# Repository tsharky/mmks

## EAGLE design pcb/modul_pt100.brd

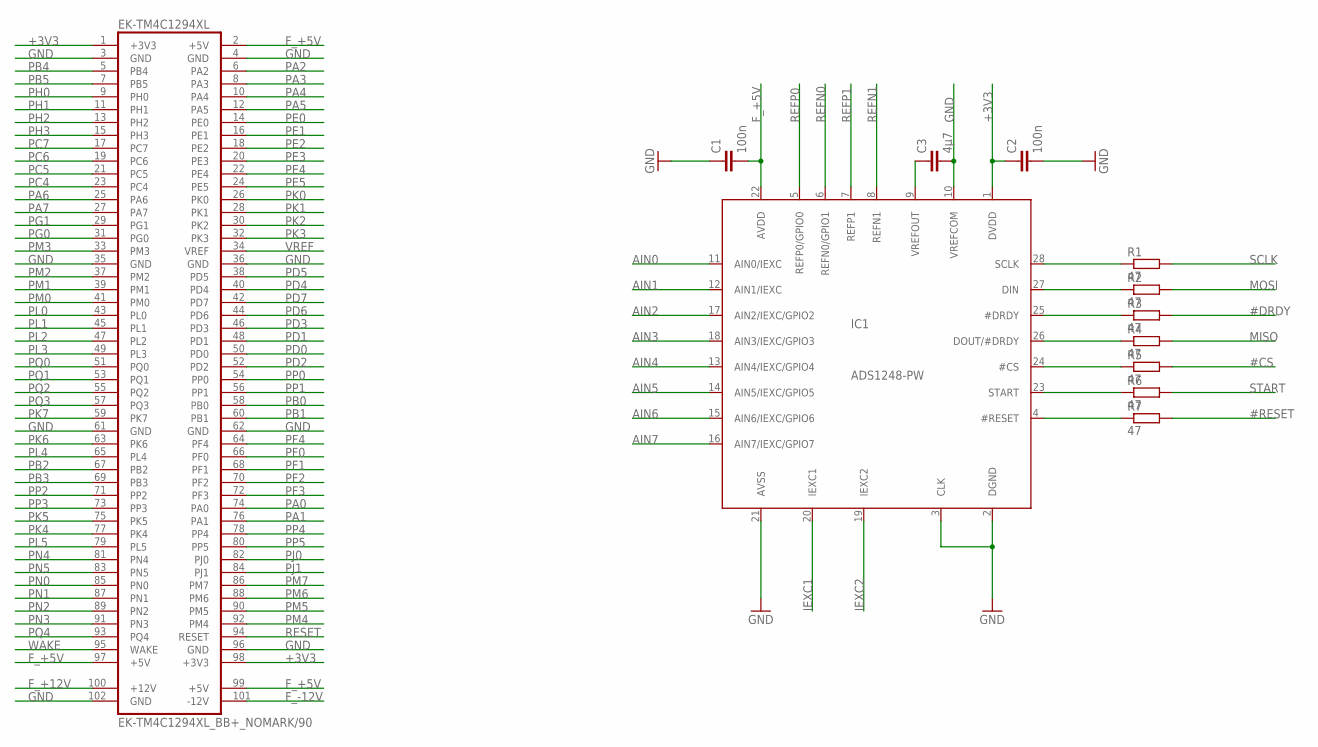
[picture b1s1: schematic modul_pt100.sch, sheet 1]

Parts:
C1, C2: 100n; C0805
C3: 4µ7; C0805
EK-TM4C1294XL: EK-TM4C1294XL_BB+_NOMARK/90
IC1: ADS1248-PW; TSSOP28
R1, R2, R3, R4, R5, R6, R7: 47; R0805

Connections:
#CS: R5.2; also elsewhere on the board
#DRDY: R3.2; also elsewhere on the board
#RESET: R7.2; also elsewhere on the board
+3V3: C2.1, EK-TM4C1294XL.1 (+3V3), EK-TM4C1294XL.98 (+3V3), IC1.1 (DVDD); also elsewhere on the board
AIN0: IC1.11 (AIN0/IEXC); also elsewhere on the board
AIN1: IC1.12 (AIN1/IEXC); also elsewhere on the board
AIN2: IC1.17 (AIN2/IEXC/GPIO2); also elsewhere on the board
AIN3: IC1.18 (AIN3/IEXC/GPIO3); also elsewhere on the board
AIN4: IC1.13 (AIN4/IEXC/GPIO4)
AIN5: IC1.14 (AIN5/IEXC/GPIO5)
AIN6: IC1.15 (AIN6/IEXC/GPIO6)
AIN7: IC1.16 (AIN7/IEXC/GPIO7)
F_+5V: C1.2, EK-TM4C1294XL.2 (+5V), EK-TM4C1294XL.97 (+5V), EK-TM4C1294XL.99 (+5V), IC1.22 (AVDD); also elsewhere on the board
F_+12V: EK-TM4C1294XL.100 (+12V); also elsewhere on the board
F_-12V: EK-TM4C1294XL.101 (-12V); also elsewhere on the board
GND: C1.1, C2.2, C3.2, EK-TM4C1294XL.3 (GND), EK-TM4C1294XL.4 (GND), EK-TM4C1294XL.35 (GND), EK-TM4C1294XL.36 (GND), EK-TM4C1294XL.61 (GND), EK-TM4C1294XL.62 (GND), EK-TM4C1294XL.96 (GND), EK-TM4C1294XL.102 (GND), IC1.2 (DGND), IC1.3 (CLK), IC1.10 (VREFCOM), IC1.21 (AVSS); also elsewhere on the board
IEXC1: IC1.20 (IEXC1); also elsewhere on the board
IEXC2: IC1.19 (IEXC2); also elsewhere on the board
MISO: R4.2; also elsewhere on the board
MOSI: R2.2; also elsewhere on the board
unnamed: C3.1, IC1.9 (VREFOUT)
unnamed: IC1.28 (SCLK), R1.1
unnamed: IC1.27 (DIN), R2.1
unnamed: IC1.25 (#DRDY), R3.1
unnamed: IC1.26 (DOUT/#DRDY), R4.1
unnamed: IC1.24 (#CS), R5.1
unnamed: IC1.23 (START), R6.1
unnamed: IC1.4 (#RESET), R7.1
PA0: EK-TM4C1294XL.74 (PA0); also elsewhere on the board
PA1: EK-TM4C1294XL.76 (PA1); also elsewhere on the board
PA2: EK-TM4C1294XL.6 (PA2); also elsewhere on the board
PA3: EK-TM4C1294XL.8 (PA3); also elsewhere on the board
PA4: EK-TM4C1294XL.10 (PA4); also elsewhere on the board
PA5: EK-TM4C1294XL.12 (PA5); also elsewhere on the board
PA6: EK-TM4C1294XL.25 (PA6); also elsewhere on the board
PA7: EK-TM4C1294XL.27 (PA7); also elsewhere on the board
PB0: EK-TM4C1294XL.58 (PB0); also elsewhere on the board
PB1: EK-TM4C1294XL.60 (PB1); also elsewhere on the board
PB2: EK-TM4C1294XL.67 (PB2); also elsewhere on the board
PB3: EK-TM4C1294XL.69 (PB3); also elsewhere on the board
PB4: EK-TM4C1294XL.5 (PB4); also elsewhere on the board
PB5: EK-TM4C1294XL.7 (PB5); also elsewhere on the board
PC4: EK-TM4C1294XL.23 (PC4); also elsewhere on the board
PC5: EK-TM4C1294XL.21 (PC5); also elsewhere on the board
PC6: EK-TM4C1294XL.19 (PC6); also elsewhere on the board
PC7: EK-TM4C1294XL.17 (PC7); also elsewhere on the board
PD0: EK-TM4C1294XL.50 (PD0); also elsewhere on the board
PD1: EK-TM4C1294XL.48 (PD1); also elsewhere on the board
PD2: EK-TM4C1294XL.52 (PD2); also elsewhere on the board
PD3: EK-TM4C1294XL.46 (PD3); also elsewhere on the board
PD4: EK-TM4C1294XL.40 (PD4); also elsewhere on the board
PD5: EK-TM4C1294XL.38 (PD5); also elsewhere on the board
PD6: EK-TM4C1294XL.44 (PD6); also elsewhere on the board
PD7: EK-TM4C1294XL.42 (PD7); also elsewhere on the board
PE0: EK-TM4C1294XL.14 (PE0); also elsewhere on the board
PE1: EK-TM4C1294XL.16 (PE1); also elsewhere on the board
PE2: EK-TM4C1294XL.18 (PE2); also elsewhere on the board
PE3: EK-TM4C1294XL.20 (PE3); also elsewhere on the board
PE4: EK-TM4C1294XL.22 (PE4); also elsewhere on the board
PE5: EK-TM4C1294XL.24 (PE5); also elsewhere on the board
PF0: EK-TM4C1294XL.66 (PF0); also elsewhere on the board
PF1: EK-TM4C1294XL.68 (PF1); also elsewhere on the board
PF2: EK-TM4C1294XL.70 (PF2); also elsewhere on the board
PF3: EK-TM4C1294XL.72 (PF3); also elsewhere on the board
PF4: EK-TM4C1294XL.64 (PF4); also elsewhere on the board
PG0: EK-TM4C1294XL.31 (PG0); also elsewhere on the board
PG1: EK-TM4C1294XL.29 (PG1); also elsewhere on the board
PH0: EK-TM4C1294XL.9 (PH0); also elsewhere on the board
PH1: EK-TM4C1294XL.11 (PH1); also elsewhere on the board
PH2: EK-TM4C1294XL.13 (PH2); also elsewhere on the board
PH3: EK-TM4C1294XL.15 (PH3); also elsewhere on the board
PJ0: EK-TM4C1294XL.82 (PJ0); also elsewhere on the board
PJ1: EK-TM4C1294XL.84 (PJ1); also elsewhere on the board
PK0: EK-TM4C1294XL.26 (PK0); also elsewhere on the board
PK1: EK-TM4C1294XL.28 (PK1); also elsewhere on the board
PK2: EK-TM4C1294XL.30 (PK2); also elsewhere on the board
PK3: EK-TM4C1294XL.32 (PK3); also elsewhere on the board
PK4: EK-TM4C1294XL.77 (PK4); also elsewhere on the board
PK5: EK-TM4C1294XL.75 (PK5); also elsewhere on the board
PK6: EK-TM4C1294XL.63 (PK6); also elsewhere on the board
PK7: EK-TM4C1294XL.59 (PK7); also elsewhere on the board
PL0: EK-TM4C1294XL.43 (PL0); also elsewhere on the board
PL1: EK-TM4C1294XL.45 (PL1); also elsewhere on the board
PL2: EK-TM4C1294XL.47 (PL2); also elsewhere on the board
PL3: EK-TM4C1294XL.49 (PL3); also elsewhere on the board
PL4: EK-TM4C1294XL.65 (PL4); also elsewhere on the board
PL5: EK-TM4C1294XL.79 (PL5); also elsewhere on the board
PM0: EK-TM4C1294XL.41 (PM0); also elsewhere on the board
PM1: EK-TM4C1294XL.39 (PM1); also elsewhere on the board
PM2: EK-TM4C1294XL.37 (PM2); also elsewhere on the board
PM3: EK-TM4C1294XL.33 (PM3); also elsewhere on the board
PM4: EK-TM4C1294XL.92 (PM4); also elsewhere on the board
PM5: EK-TM4C1294XL.90 (PM5); also elsewhere on the board
PM6: EK-TM4C1294XL.88 (PM6); also elsewhere on the board
PM7: EK-TM4C1294XL.86 (PM7); also elsewhere on the board
PN0: EK-TM4C1294XL.85 (PN0); also elsewhere on the board
PN1: EK-TM4C1294XL.87 (PN1); also elsewhere on the board
PN2: EK-TM4C1294XL.89 (PN2); also elsewhere on the board
PN3: EK-TM4C1294XL.91 (PN3); also elsewhere on the board
PN4: EK-TM4C1294XL.81 (PN4); also elsewhere on the board
PN5: EK-TM4C1294XL.83 (PN5); also elsewhere on the board
PP0: EK-TM4C1294XL.54 (PP0); also elsewhere on the board
PP1: EK-TM4C1294XL.56 (PP1); also elsewhere on the board
PP2: EK-TM4C1294XL.71 (PP2); also elsewhere on the board
PP3: EK-TM4C1294XL.73 (PP3); also elsewhere on the board
PP4: EK-TM4C1294XL.78 (PP4); also elsewhere on the board
PP5: EK-TM4C1294XL.80 (PP5); also elsewhere on the board
PQ0: EK-TM4C1294XL.51 (PQ0); also elsewhere on the board
PQ1: EK-TM4C1294XL.53 (PQ1); also elsewhere on the board
PQ2: EK-TM4C1294XL.55 (PQ2); also elsewhere on the board
PQ3: EK-TM4C1294XL.57 (PQ3); also elsewhere on the board
PQ4: EK-TM4C1294XL.93 (PQ4); also elsewhere on the board
REFN0: IC1.6 (REFN0/GPIO1); also elsewhere on the board
REFN1: IC1.8 (REFN1); also elsewhere on the board
REFP0: IC1.5 (REFP0/GPIO0); also elsewhere on the board
REFP1: IC1.7 (REFP1); also elsewhere on the board
RESET: EK-TM4C1294XL.94 (RESET); also elsewhere on the board
SCLK: R1.2; also elsewhere on the board
START: R6.2; also elsewhere on the board
VREF: EK-TM4C1294XL.34 (VREF); also elsewhere on the board
WAKE: EK-TM4C1294XL.95 (WAKE); also elsewhere on the board

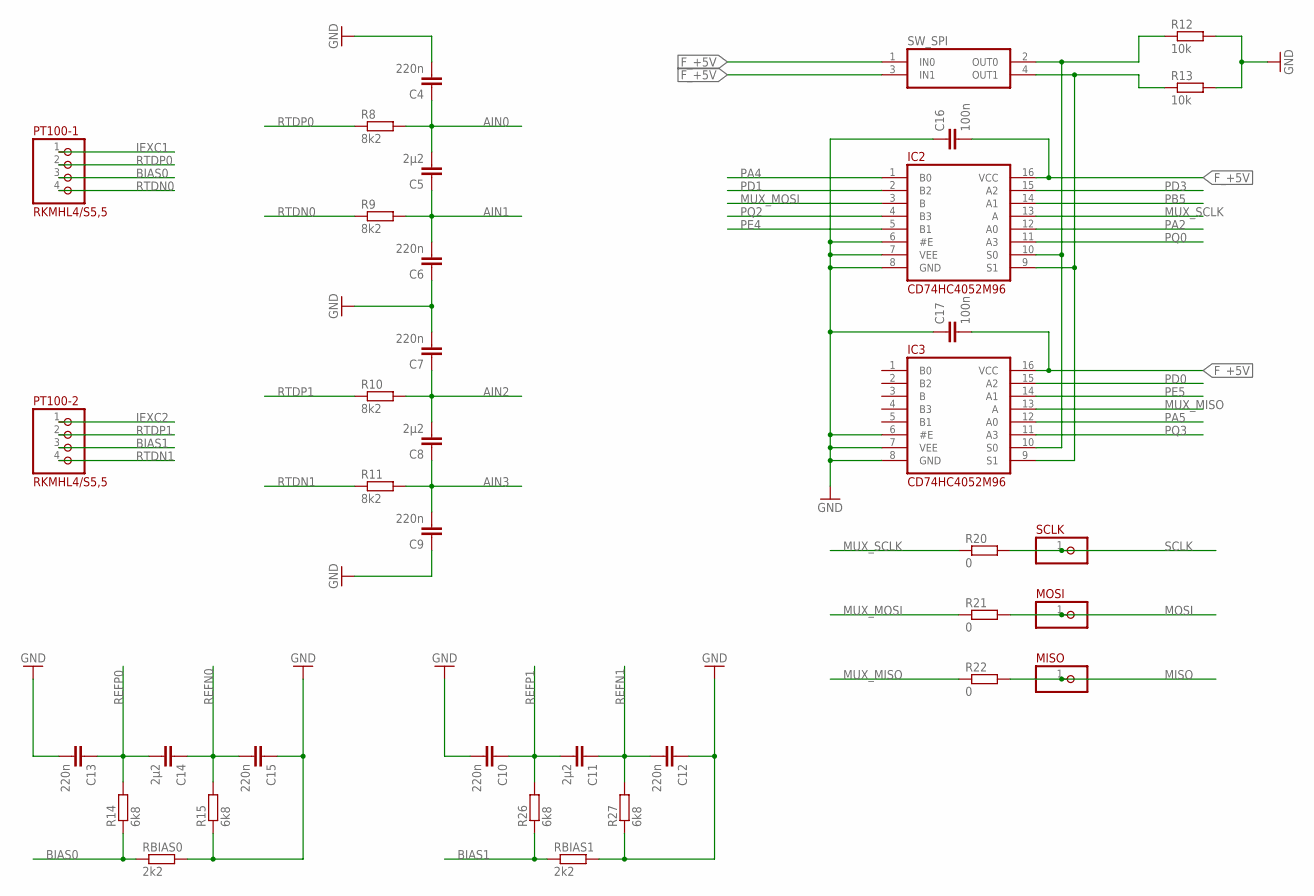
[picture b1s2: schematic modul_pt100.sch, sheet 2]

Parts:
C4, C6, C7, C9, C10, C12, C13, C15: 220n; C0805
C5, C8, C11, C14: 2µ2; C0805
C16, C17: 100n; C0805
IC2, IC3: CD74HC4052M96; SOIC16_D
MISO: PINH-1X1; 1X1
MOSI: PINH-1X1; 1X1
PT100-1, PT100-2: RKMHL4/S5,5
R8, R9, R10, R11: 8k2; R0805
R12, R13: 10k; R0805
R14, R15, R26, R27: 6k8; R0805
R20, R21, R22: 0; R0805
RBIAS0, RBIAS1: 2k2; R0805
SCLK: PINH-1X1; 1X1
SW_SPI: NT02

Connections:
AIN0: C4.1, C5.2, R8.2; also elsewhere on the board
AIN1: C5.1, C6.2, R9.2; also elsewhere on the board
AIN2: C7.1, C8.2, R10.2; also elsewhere on the board
AIN3: C8.1, C9.2, R11.2; also elsewhere on the board
BIAS0: PT100-1.3, R14.1, RBIAS0.1
BIAS1: PT100-2.3, R26.1, RBIAS1.1
F_+5V: C16.2, C17.2, IC2.16 (VCC), IC3.16 (VCC), SW_SPI.1 (IN0), SW_SPI.3 (IN1); also elsewhere on the board
GND: C4.2, C6.1, C7.2, C9.1, C10.2, C12.1, C13.2, C15.1, C16.1, C17.1, IC2.6 (#E), IC2.7 (VEE), IC2.8 (GND), IC3.6 (#E), IC3.7 (VEE), IC3.8 (GND), R12.2, R13.2, R15.1, R27.1, RBIAS0.2, RBIAS1.2; also elsewhere on the board
IEXC1: PT100-1.1; also elsewhere on the board
IEXC2: PT100-2.1; also elsewhere on the board
MISO: MISO.1, R22.2; also elsewhere on the board
MOSI: MOSI.1, R21.2; also elsewhere on the board
MUX_MISO: IC3.13 (A), R22.1
MUX_MOSI: IC2.3 (B), R21.1
MUX_SCLK: IC2.13 (A), R20.1
unnamed: IC2.10 (S0), IC3.10 (S0), R12.1, SW_SPI.2 (OUT0)
unnamed: IC2.9 (S1), IC3.9 (S1), R13.1, SW_SPI.4 (OUT1)
PA2: IC2.12 (A0); also elsewhere on the board
PA4: IC2.1 (B0); also elsewhere on the board
PA5: IC3.12 (A0); also elsewhere on the board
PB5: IC2.14 (A1); also elsewhere on the board
PD0: IC3.15 (A2); also elsewhere on the board
PD1: IC2.2 (B2); also elsewhere on the board
PD3: IC2.15 (A2); also elsewhere on the board
PE4: IC2.5 (B1); also elsewhere on the board
PE5: IC3.14 (A1); also elsewhere on the board
PQ0: IC2.11 (A3); also elsewhere on the board
PQ2: IC2.4 (B3); also elsewhere on the board
PQ3: IC3.11 (A3); also elsewhere on the board
REFN0: C14.1, C15.2, R15.2; also elsewhere on the board
REFN1: C11.1, C12.2, R27.2; also elsewhere on the board
REFP0: C13.1, C14.2, R14.2; also elsewhere on the board
REFP1: C10.1, C11.2, R26.2; also elsewhere on the board
RTDN0: PT100-1.4, R9.1
RTDN1: PT100-2.4, R11.1
RTDP0: PT100-1.2, R8.1
RTDP1: PT100-2.2, R10.1
SCLK: R20.2, SCLK.1; also elsewhere on the board

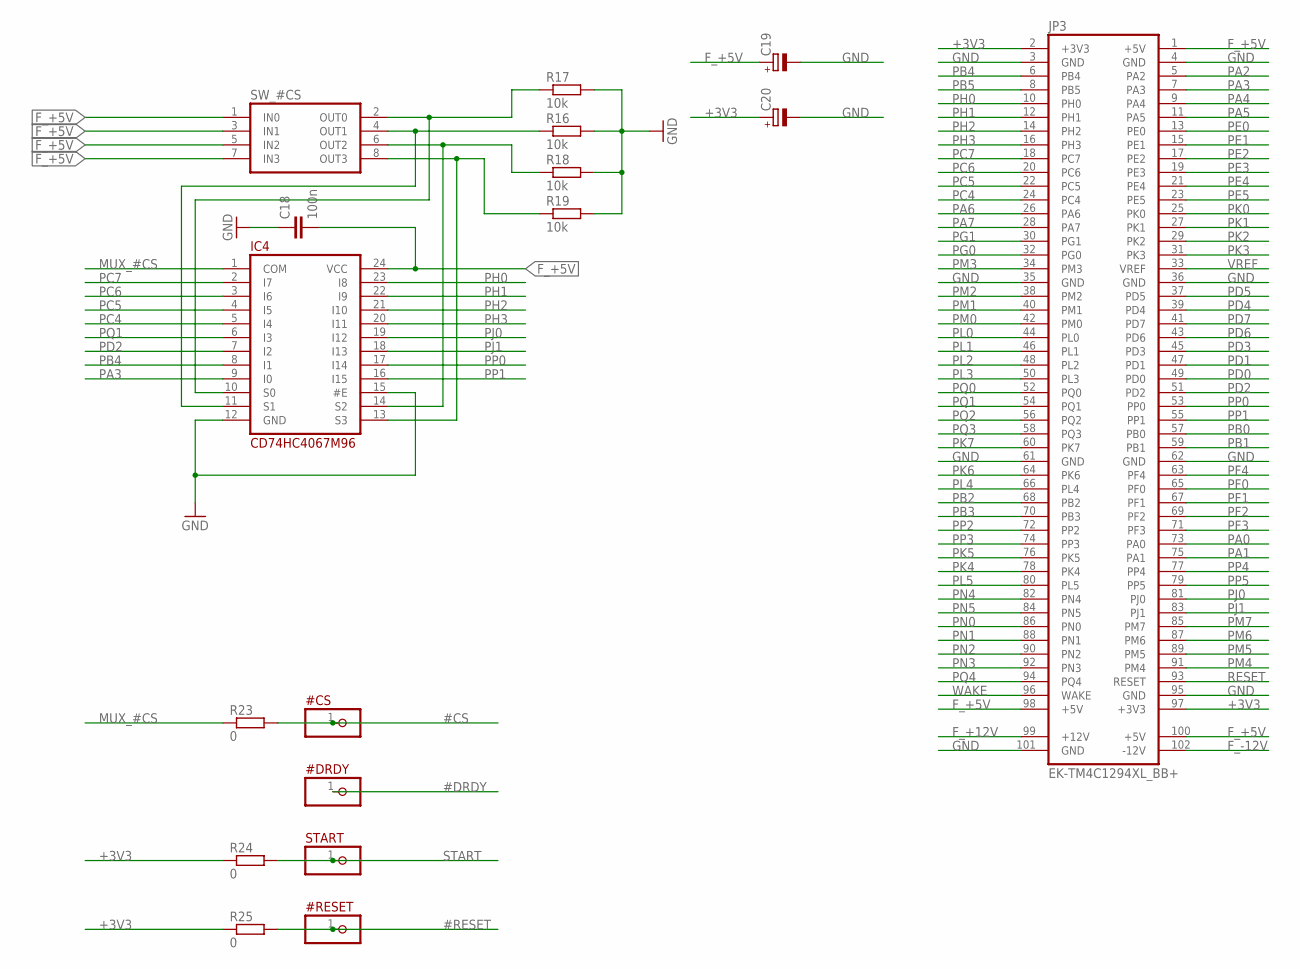
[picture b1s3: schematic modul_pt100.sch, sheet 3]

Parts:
#CS: PINH-1X1; 1X1
#DRDY: PINH-1X1; 1X1
#RESET: PINH-1X1; 1X1
C18: 100n; C0805
C19, C20: CPOL-EUE2.5-6; E2,5-6
IC4: CD74HC4067M96; SOIC24_DW
JP3: EK-TM4C1294XL_BB+
R16, R17, R18, R19: 10k; R0805
R23, R24, R25: 0; R0805
START: PINH-1X1; 1X1
SW_#CS: NT04

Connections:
#CS: #CS.1, R23.2; also elsewhere on the board
#DRDY: #DRDY.1; also elsewhere on the board
#RESET: #RESET.1, R25.2; also elsewhere on the board
+3V3: C20.+, JP3.2 (+3V3), JP3.97 (+3V3), R24.1, R25.1; also elsewhere on the board
F_+5V: C18.2, C19.+, IC4.24 (VCC), JP3.1 (+5V), JP3.98 (+5V), JP3.100 (+5V), SW_#CS.1 (IN0), SW_#CS.3 (IN1), SW_#CS.5 (IN2), SW_#CS.7 (IN3); also elsewhere on the board
F_+12V: JP3.99 (+12V); also elsewhere on the board
F_-12V: JP3.102 (-12V); also elsewhere on the board
GND: C18.1, C19.-, C20.-, IC4.12 (GND), IC4.15 (#E), JP3.3 (GND), JP3.4 (GND), JP3.35 (GND), JP3.36 (GND), JP3.61 (GND), JP3.62 (GND), JP3.95 (GND), JP3.101 (GND), R16.2, R17.2, R18.2, R19.2; also elsewhere on the board
MUX_#CS: IC4.1 (COM), R23.1
unnamed: IC4.11 (S1), R16.1, SW_#CS.4 (OUT1)
unnamed: IC4.10 (S0), R17.1, SW_#CS.2 (OUT0)
unnamed: IC4.14 (S2), R18.1, SW_#CS.6 (OUT2)
unnamed: IC4.13 (S3), R19.1, SW_#CS.8 (OUT3)
PA0: JP3.73 (PA0); also elsewhere on the board
PA1: JP3.75 (PA1); also elsewhere on the board
PA2: JP3.5 (PA2); also elsewhere on the board
PA3: IC4.9 (I0), JP3.7 (PA3); also elsewhere on the board
PA4: JP3.9 (PA4); also elsewhere on the board
PA5: JP3.11 (PA5); also elsewhere on the board
PA6: JP3.26 (PA6); also elsewhere on the board
PA7: JP3.28 (PA7); also elsewhere on the board
PB0: JP3.57 (PB0); also elsewhere on the board
PB1: JP3.59 (PB1); also elsewhere on the board
PB2: JP3.68 (PB2); also elsewhere on the board
PB3: JP3.70 (PB3); also elsewhere on the board
PB4: IC4.8 (I1), JP3.6 (PB4); also elsewhere on the board
PB5: JP3.8 (PB5); also elsewhere on the board
PC4: IC4.5 (I4), JP3.24 (PC4); also elsewhere on the board
PC5: IC4.4 (I5), JP3.22 (PC5); also elsewhere on the board
PC6: IC4.3 (I6), JP3.20 (PC6); also elsewhere on the board
PC7: IC4.2 (I7), JP3.18 (PC7); also elsewhere on the board
PD0: JP3.49 (PD0); also elsewhere on the board
PD1: JP3.47 (PD1); also elsewhere on the board
PD2: IC4.7 (I2), JP3.51 (PD2); also elsewhere on the board
PD3: JP3.45 (PD3); also elsewhere on the board
PD4: JP3.39 (PD4); also elsewhere on the board
PD5: JP3.37 (PD5); also elsewhere on the board
PD6: JP3.43 (PD6); also elsewhere on the board
PD7: JP3.41 (PD7); also elsewhere on the board
PE0: JP3.13 (PE0); also elsewhere on the board
PE1: JP3.15 (PE1); also elsewhere on the board
PE2: JP3.17 (PE2); also elsewhere on the board
PE3: JP3.19 (PE3); also elsewhere on the board
PE4: JP3.21 (PE4); also elsewhere on the board
PE5: JP3.23 (PE5); also elsewhere on the board
PF0: JP3.65 (PF0); also elsewhere on the board
PF1: JP3.67 (PF1); also elsewhere on the board
PF2: JP3.69 (PF2); also elsewhere on the board
PF3: JP3.71 (PF3); also elsewhere on the board
PF4: JP3.63 (PF4); also elsewhere on the board
PG0: JP3.32 (PG0); also elsewhere on the board
PG1: JP3.30 (PG1); also elsewhere on the board
PH0: IC4.23 (I8), JP3.10 (PH0); also elsewhere on the board
PH1: IC4.22 (I9), JP3.12 (PH1); also elsewhere on the board
PH2: IC4.21 (I10), JP3.14 (PH2); also elsewhere on the board
PH3: IC4.20 (I11), JP3.16 (PH3); also elsewhere on the board
PJ0: IC4.19 (I12), JP3.81 (PJ0); also elsewhere on the board
PJ1: IC4.18 (I13), JP3.83 (PJ1); also elsewhere on the board
PK0: JP3.25 (PK0); also elsewhere on the board
PK1: JP3.27 (PK1); also elsewhere on the board
PK2: JP3.29 (PK2); also elsewhere on the board
PK3: JP3.31 (PK3); also elsewhere on the board
PK4: JP3.78 (PK4); also elsewhere on the board
PK5: JP3.76 (PK5); also elsewhere on the board
PK6: JP3.64 (PK6); also elsewhere on the board
PK7: JP3.60 (PK7); also elsewhere on the board
PL0: JP3.44 (PL0); also elsewhere on the board
PL1: JP3.46 (PL1); also elsewhere on the board
PL2: JP3.48 (PL2); also elsewhere on the board
PL3: JP3.50 (PL3); also elsewhere on the board
PL4: JP3.66 (PL4); also elsewhere on the board
PL5: JP3.80 (PL5); also elsewhere on the board
PM0: JP3.42 (PM0); also elsewhere on the board
PM1: JP3.40 (PM1); also elsewhere on the board
PM2: JP3.38 (PM2); also elsewhere on the board
PM3: JP3.34 (PM3); also elsewhere on the board
PM4: JP3.91 (PM4); also elsewhere on the board
PM5: JP3.89 (PM5); also elsewhere on the board
PM6: JP3.87 (PM6); also elsewhere on the board
PM7: JP3.85 (PM7); also elsewhere on the board
PN0: JP3.86 (PN0); also elsewhere on the board
PN1: JP3.88 (PN1); also elsewhere on the board
PN2: JP3.90 (PN2); also elsewhere on the board
PN3: JP3.92 (PN3); also elsewhere on the board
PN4: JP3.82 (PN4); also elsewhere on the board
PN5: JP3.84 (PN5); also elsewhere on the board
PP0: IC4.17 (I14), JP3.53 (PP0); also elsewhere on the board
PP1: IC4.16 (I15), JP3.55 (PP1); also elsewhere on the board
PP2: JP3.72 (PP2); also elsewhere on the board
PP3: JP3.74 (PP3); also elsewhere on the board
PP4: JP3.77 (PP4); also elsewhere on the board
PP5: JP3.79 (PP5); also elsewhere on the board
PQ0: JP3.52 (PQ0); also elsewhere on the board
PQ1: IC4.6 (I3), JP3.54 (PQ1); also elsewhere on the board
PQ2: JP3.56 (PQ2); also elsewhere on the board
PQ3: JP3.58 (PQ3); also elsewhere on the board
PQ4: JP3.94 (PQ4); also elsewhere on the board
RESET: JP3.93 (RESET); also elsewhere on the board
START: R24.2, START.1; also elsewhere on the board
VREF: JP3.33 (VREF); also elsewhere on the board
WAKE: JP3.96 (WAKE); also elsewhere on the board

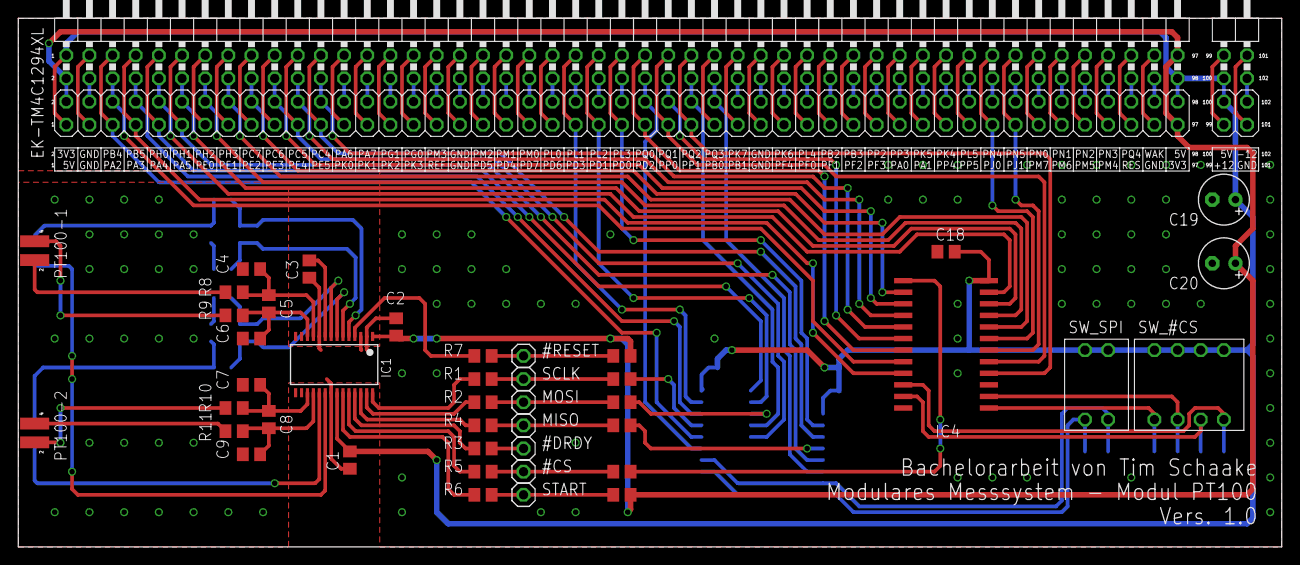
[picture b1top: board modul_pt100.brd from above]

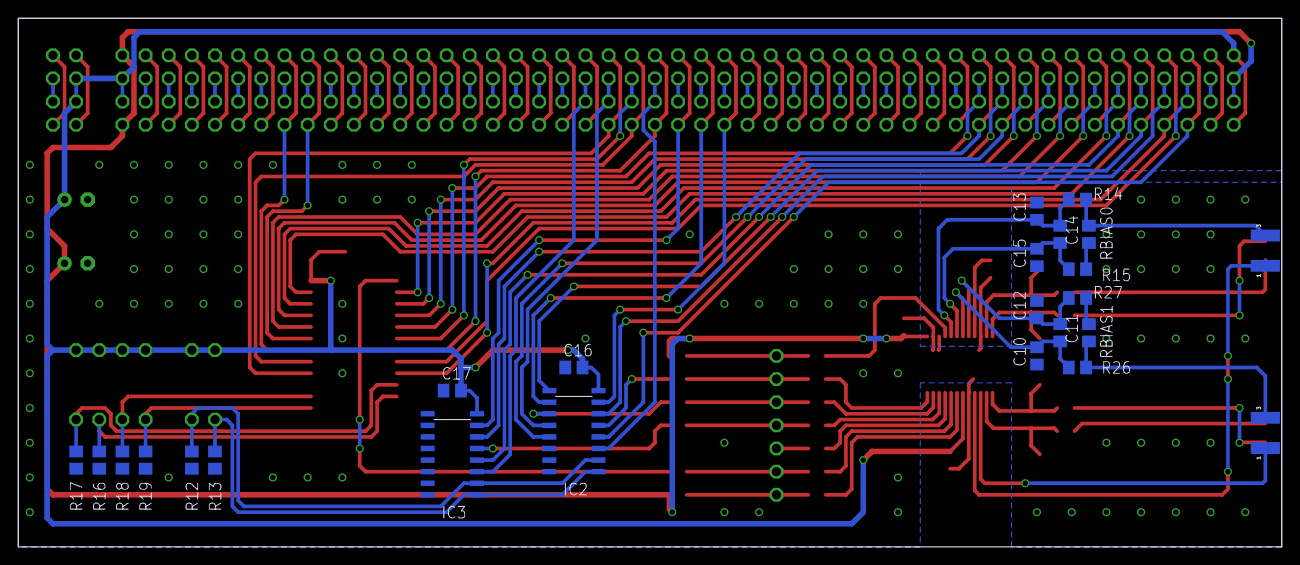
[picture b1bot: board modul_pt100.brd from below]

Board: 2 copper layers, 138.6 x 58.0 mm, 66 parts (22 on the bottom side), 133 nets.

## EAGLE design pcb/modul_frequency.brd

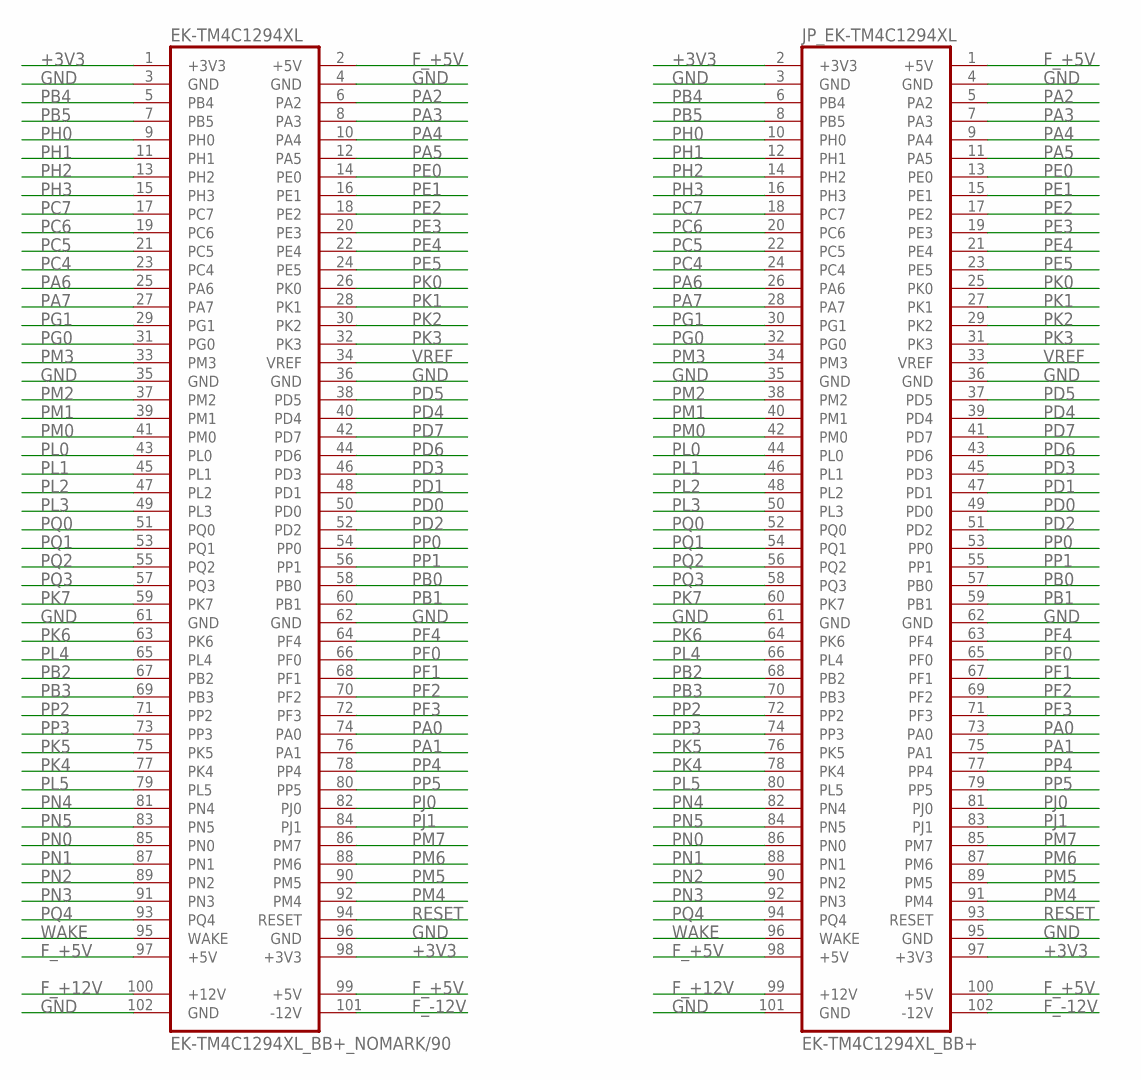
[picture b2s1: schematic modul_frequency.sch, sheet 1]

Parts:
EK-TM4C1294XL: EK-TM4C1294XL_BB+_NOMARK/90
JP_EK-TM4C1294XL: EK-TM4C1294XL_BB+

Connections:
+3V3: EK-TM4C1294XL.1 (+3V3), EK-TM4C1294XL.98 (+3V3), JP_EK-TM4C1294XL.2 (+3V3), JP_EK-TM4C1294XL.97 (+3V3); also elsewhere on the board
F_+5V: EK-TM4C1294XL.2 (+5V), EK-TM4C1294XL.97 (+5V), EK-TM4C1294XL.99 (+5V), JP_EK-TM4C1294XL.1 (+5V), JP_EK-TM4C1294XL.98 (+5V), JP_EK-TM4C1294XL.100 (+5V); also elsewhere on the board
F_+12V: EK-TM4C1294XL.100 (+12V), JP_EK-TM4C1294XL.99 (+12V); also elsewhere on the board
F_-12V: EK-TM4C1294XL.101 (-12V), JP_EK-TM4C1294XL.102 (-12V)
GND: EK-TM4C1294XL.3 (GND), EK-TM4C1294XL.4 (GND), EK-TM4C1294XL.35 (GND), EK-TM4C1294XL.36 (GND), EK-TM4C1294XL.61 (GND), EK-TM4C1294XL.62 (GND), EK-TM4C1294XL.96 (GND), EK-TM4C1294XL.102 (GND), JP_EK-TM4C1294XL.3 (GND), JP_EK-TM4C1294XL.4 (GND), JP_EK-TM4C1294XL.35 (GND), JP_EK-TM4C1294XL.36 (GND), JP_EK-TM4C1294XL.61 (GND), JP_EK-TM4C1294XL.62 (GND), JP_EK-TM4C1294XL.95 (GND), JP_EK-TM4C1294XL.101 (GND); also elsewhere on the board
PA0: EK-TM4C1294XL.74 (PA0), JP_EK-TM4C1294XL.73 (PA0); also elsewhere on the board
PA1: EK-TM4C1294XL.76 (PA1), JP_EK-TM4C1294XL.75 (PA1); also elsewhere on the board
PA2: EK-TM4C1294XL.6 (PA2), JP_EK-TM4C1294XL.5 (PA2); also elsewhere on the board
PA3: EK-TM4C1294XL.8 (PA3), JP_EK-TM4C1294XL.7 (PA3); also elsewhere on the board
PA4: EK-TM4C1294XL.10 (PA4), JP_EK-TM4C1294XL.9 (PA4); also elsewhere on the board
PA5: EK-TM4C1294XL.12 (PA5), JP_EK-TM4C1294XL.11 (PA5); also elsewhere on the board
PA6: EK-TM4C1294XL.25 (PA6), JP_EK-TM4C1294XL.26 (PA6); also elsewhere on the board
PA7: EK-TM4C1294XL.27 (PA7), JP_EK-TM4C1294XL.28 (PA7); also elsewhere on the board
PB0: EK-TM4C1294XL.58 (PB0), JP_EK-TM4C1294XL.57 (PB0)
PB1: EK-TM4C1294XL.60 (PB1), JP_EK-TM4C1294XL.59 (PB1)
PB2: EK-TM4C1294XL.67 (PB2), JP_EK-TM4C1294XL.68 (PB2)
PB3: EK-TM4C1294XL.69 (PB3), JP_EK-TM4C1294XL.70 (PB3)
PB4: EK-TM4C1294XL.5 (PB4), JP_EK-TM4C1294XL.6 (PB4)
PB5: EK-TM4C1294XL.7 (PB5), JP_EK-TM4C1294XL.8 (PB5)
PC4: EK-TM4C1294XL.23 (PC4), JP_EK-TM4C1294XL.24 (PC4)
PC5: EK-TM4C1294XL.21 (PC5), JP_EK-TM4C1294XL.22 (PC5)
PC6: EK-TM4C1294XL.19 (PC6), JP_EK-TM4C1294XL.20 (PC6)
PC7: EK-TM4C1294XL.17 (PC7), JP_EK-TM4C1294XL.18 (PC7)
PD0: EK-TM4C1294XL.50 (PD0), JP_EK-TM4C1294XL.49 (PD0); also elsewhere on the board
PD1: EK-TM4C1294XL.48 (PD1), JP_EK-TM4C1294XL.47 (PD1); also elsewhere on the board
PD2: EK-TM4C1294XL.52 (PD2), JP_EK-TM4C1294XL.51 (PD2); also elsewhere on the board
PD3: EK-TM4C1294XL.46 (PD3), JP_EK-TM4C1294XL.45 (PD3); also elsewhere on the board
PD4: EK-TM4C1294XL.40 (PD4), JP_EK-TM4C1294XL.39 (PD4); also elsewhere on the board
PD5: EK-TM4C1294XL.38 (PD5), JP_EK-TM4C1294XL.37 (PD5); also elsewhere on the board
PD6: EK-TM4C1294XL.44 (PD6), JP_EK-TM4C1294XL.43 (PD6)
PD7: EK-TM4C1294XL.42 (PD7), JP_EK-TM4C1294XL.41 (PD7)
PE0: EK-TM4C1294XL.14 (PE0), JP_EK-TM4C1294XL.13 (PE0)
PE1: EK-TM4C1294XL.16 (PE1), JP_EK-TM4C1294XL.15 (PE1)
PE2: EK-TM4C1294XL.18 (PE2), JP_EK-TM4C1294XL.17 (PE2)
PE3: EK-TM4C1294XL.20 (PE3), JP_EK-TM4C1294XL.19 (PE3)
PE4: EK-TM4C1294XL.22 (PE4), JP_EK-TM4C1294XL.21 (PE4)
PE5: EK-TM4C1294XL.24 (PE5), JP_EK-TM4C1294XL.23 (PE5)
PF0: EK-TM4C1294XL.66 (PF0), JP_EK-TM4C1294XL.65 (PF0)
PF1: EK-TM4C1294XL.68 (PF1), JP_EK-TM4C1294XL.67 (PF1)
PF2: EK-TM4C1294XL.70 (PF2), JP_EK-TM4C1294XL.69 (PF2)
PF3: EK-TM4C1294XL.72 (PF3), JP_EK-TM4C1294XL.71 (PF3)
PF4: EK-TM4C1294XL.64 (PF4), JP_EK-TM4C1294XL.63 (PF4)
PG0: EK-TM4C1294XL.31 (PG0), JP_EK-TM4C1294XL.32 (PG0)
PG1: EK-TM4C1294XL.29 (PG1), JP_EK-TM4C1294XL.30 (PG1)
PH0: EK-TM4C1294XL.9 (PH0), JP_EK-TM4C1294XL.10 (PH0)
PH1: EK-TM4C1294XL.11 (PH1), JP_EK-TM4C1294XL.12 (PH1)
PH2: EK-TM4C1294XL.13 (PH2), JP_EK-TM4C1294XL.14 (PH2)
PH3: EK-TM4C1294XL.15 (PH3), JP_EK-TM4C1294XL.16 (PH3)
PJ0: EK-TM4C1294XL.82 (PJ0), JP_EK-TM4C1294XL.81 (PJ0)
PJ1: EK-TM4C1294XL.84 (PJ1), JP_EK-TM4C1294XL.83 (PJ1)
PK0: EK-TM4C1294XL.26 (PK0), JP_EK-TM4C1294XL.25 (PK0); also elsewhere on the board
PK1: EK-TM4C1294XL.28 (PK1), JP_EK-TM4C1294XL.27 (PK1); also elsewhere on the board
PK2: EK-TM4C1294XL.30 (PK2), JP_EK-TM4C1294XL.29 (PK2); also elsewhere on the board
PK3: EK-TM4C1294XL.32 (PK3), JP_EK-TM4C1294XL.31 (PK3); also elsewhere on the board
PK4: EK-TM4C1294XL.77 (PK4), JP_EK-TM4C1294XL.78 (PK4)
PK5: EK-TM4C1294XL.75 (PK5), JP_EK-TM4C1294XL.76 (PK5)
PK6: EK-TM4C1294XL.63 (PK6), JP_EK-TM4C1294XL.64 (PK6)
PK7: EK-TM4C1294XL.59 (PK7), JP_EK-TM4C1294XL.60 (PK7)
PL0: EK-TM4C1294XL.43 (PL0), JP_EK-TM4C1294XL.44 (PL0)
PL1: EK-TM4C1294XL.45 (PL1), JP_EK-TM4C1294XL.46 (PL1)
PL2: EK-TM4C1294XL.47 (PL2), JP_EK-TM4C1294XL.48 (PL2)
PL3: EK-TM4C1294XL.49 (PL3), JP_EK-TM4C1294XL.50 (PL3)
PL4: EK-TM4C1294XL.65 (PL4), JP_EK-TM4C1294XL.66 (PL4); also elsewhere on the board
PL5: EK-TM4C1294XL.79 (PL5), JP_EK-TM4C1294XL.80 (PL5); also elsewhere on the board
PM0: EK-TM4C1294XL.41 (PM0), JP_EK-TM4C1294XL.42 (PM0); also elsewhere on the board
PM1: EK-TM4C1294XL.39 (PM1), JP_EK-TM4C1294XL.40 (PM1); also elsewhere on the board
PM2: EK-TM4C1294XL.37 (PM2), JP_EK-TM4C1294XL.38 (PM2); also elsewhere on the board
PM3: EK-TM4C1294XL.33 (PM3), JP_EK-TM4C1294XL.34 (PM3); also elsewhere on the board
PM4: EK-TM4C1294XL.92 (PM4), JP_EK-TM4C1294XL.91 (PM4); also elsewhere on the board
PM5: EK-TM4C1294XL.90 (PM5), JP_EK-TM4C1294XL.89 (PM5); also elsewhere on the board
PM6: EK-TM4C1294XL.88 (PM6), JP_EK-TM4C1294XL.87 (PM6); also elsewhere on the board
PM7: EK-TM4C1294XL.86 (PM7), JP_EK-TM4C1294XL.85 (PM7); also elsewhere on the board
PN0: EK-TM4C1294XL.85 (PN0), JP_EK-TM4C1294XL.86 (PN0)
PN1: EK-TM4C1294XL.87 (PN1), JP_EK-TM4C1294XL.88 (PN1)
PN2: EK-TM4C1294XL.89 (PN2), JP_EK-TM4C1294XL.90 (PN2)
PN3: EK-TM4C1294XL.91 (PN3), JP_EK-TM4C1294XL.92 (PN3)
PN4: EK-TM4C1294XL.81 (PN4), JP_EK-TM4C1294XL.82 (PN4)
PN5: EK-TM4C1294XL.83 (PN5), JP_EK-TM4C1294XL.84 (PN5)
PP0: EK-TM4C1294XL.54 (PP0), JP_EK-TM4C1294XL.53 (PP0)
PP1: EK-TM4C1294XL.56 (PP1), JP_EK-TM4C1294XL.55 (PP1)
PP2: EK-TM4C1294XL.71 (PP2), JP_EK-TM4C1294XL.72 (PP2)
PP3: EK-TM4C1294XL.73 (PP3), JP_EK-TM4C1294XL.74 (PP3)
PP4: EK-TM4C1294XL.78 (PP4), JP_EK-TM4C1294XL.77 (PP4)
PP5: EK-TM4C1294XL.80 (PP5), JP_EK-TM4C1294XL.79 (PP5)
PQ0: EK-TM4C1294XL.51 (PQ0), JP_EK-TM4C1294XL.52 (PQ0)
PQ1: EK-TM4C1294XL.53 (PQ1), JP_EK-TM4C1294XL.54 (PQ1)
PQ2: EK-TM4C1294XL.55 (PQ2), JP_EK-TM4C1294XL.56 (PQ2)
PQ3: EK-TM4C1294XL.57 (PQ3), JP_EK-TM4C1294XL.58 (PQ3)
PQ4: EK-TM4C1294XL.93 (PQ4), JP_EK-TM4C1294XL.94 (PQ4)
RESET: EK-TM4C1294XL.94 (RESET), JP_EK-TM4C1294XL.93 (RESET)
VREF: EK-TM4C1294XL.34 (VREF), JP_EK-TM4C1294XL.33 (VREF)
WAKE: EK-TM4C1294XL.95 (WAKE), JP_EK-TM4C1294XL.96 (WAKE)

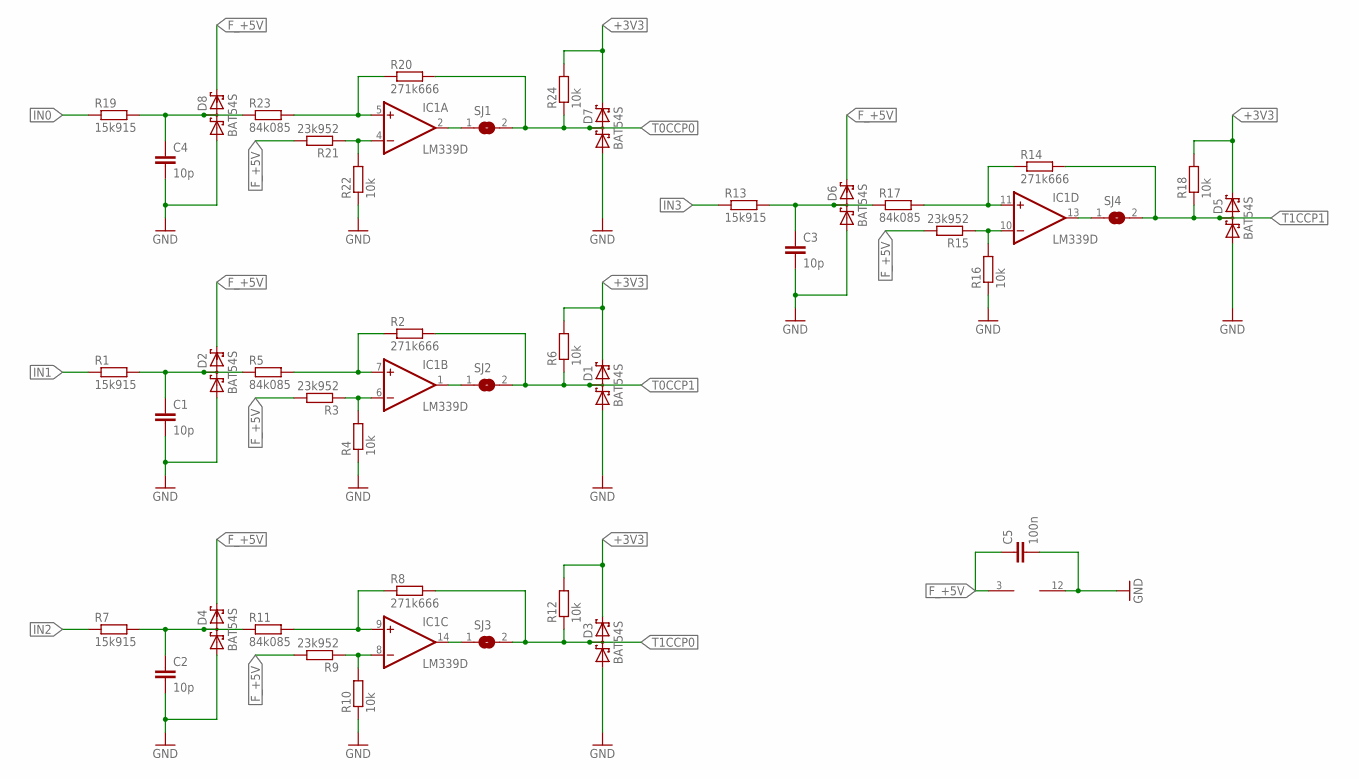
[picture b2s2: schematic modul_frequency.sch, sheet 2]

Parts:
C1, C2, C3, C4: 10p; C0805
C5: 100n; C0805
D1, D2, D3, D4, D5, D6, D7, D8: BAT54S; SOT23
IC1: LM339D; SO14
R1, R7, R13, R19: 15k915; R0805
R2, R8, R14, R20: 271k666; R0805
R3, R9, R15, R21: 23k952; R0805
R4, R6, R10, R12, R16, R18, R22, R24: 10k; R0805
R5, R11, R17, R23: 84k085; R0805
SJ1, SJ2, SJ3, SJ4: SJ

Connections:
+3V3: D1.2 (C2), D3.2 (C2), D5.2 (C2), D7.2 (C2), R6.2, R12.2, R18.2, R24.2; also elsewhere on the board
F_+5V: C5.1, D2.2 (C2), D4.2 (C2), D6.2 (C2), D8.2 (C2), IC1.3 (V+), R3.2, R9.2, R15.2, R21.2; also elsewhere on the board
GND: C1.2, C2.2, C3.2, C4.2, C5.2, D1.1 (A1), D2.1 (A1), D3.1 (A1), D4.1 (A1), D5.1 (A1), D6.1 (A1), D7.1 (A1), D8.1 (A1), IC1.12 (GND), R4.1, R10.1, R16.1, R22.1; also elsewhere on the board
IN0: R19.1; also elsewhere on the board
IN1: R1.1; also elsewhere on the board
IN2: R7.1; also elsewhere on the board
IN3: R13.1; also elsewhere on the board
unnamed: IC1.2 (OUT), SJ1.1
unnamed: IC1.7 (+IN), R2.1, R5.2
unnamed: IC1.6 (-IN), R3.1, R4.2
unnamed: C1.1, D2.3 (C1A2), R1.2, R5.1
unnamed: IC1.1 (OUT), SJ2.1
unnamed: IC1.9 (+IN), R8.1, R11.2
unnamed: IC1.8 (-IN), R9.1, R10.2
unnamed: C2.1, D4.3 (C1A2), R7.2, R11.1
unnamed: IC1.5 (+IN), R20.1, R23.2
unnamed: IC1.4 (-IN), R21.1, R22.2
unnamed: C4.1, D8.3 (C1A2), R19.2, R23.1
unnamed: IC1.14 (OUT), SJ3.1
unnamed: IC1.11 (+IN), R14.1, R17.2
unnamed: IC1.10 (-IN), R15.1, R16.2
unnamed: C3.1, D6.3 (C1A2), R13.2, R17.1
unnamed: IC1.13 (OUT), SJ4.1
T0CCP0: D7.3 (C1A2), R20.2, R24.1, SJ1.2; also elsewhere on the board
T0CCP1: D1.3 (C1A2), R2.2, R6.1, SJ2.2; also elsewhere on the board
T1CCP0: D3.3 (C1A2), R8.2, R12.1, SJ3.2; also elsewhere on the board
T1CCP1: D5.3 (C1A2), R14.2, R18.1, SJ4.2; also elsewhere on the board
